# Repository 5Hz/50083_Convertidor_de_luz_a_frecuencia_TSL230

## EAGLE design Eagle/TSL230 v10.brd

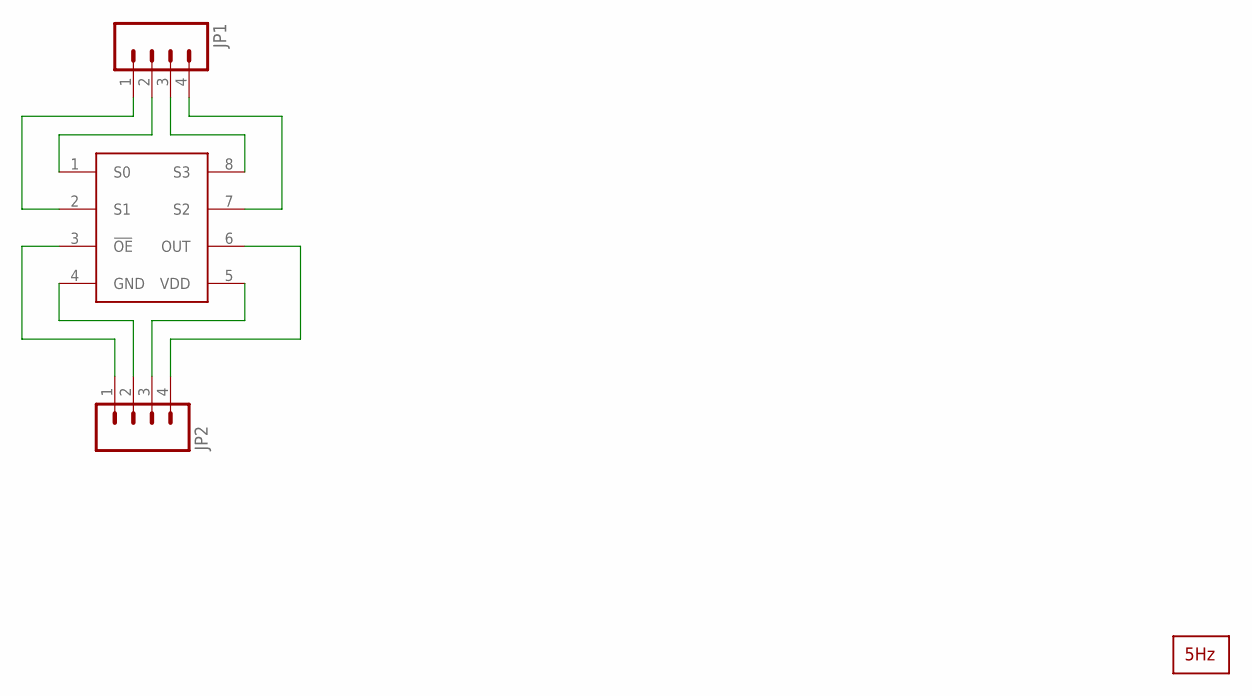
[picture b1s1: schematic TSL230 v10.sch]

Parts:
JP1, JP2: M04PTH; 1X04
U$1: TSL230RD; SOIC8
U$2: LOGO2_SILKL5MM; LARGO2_5MM

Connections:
unnamed: JP2.1, U$1.3 (!OE)
unnamed: JP2.2, U$1.4 (GND)
unnamed: JP2.4, U$1.6 (OUT)
unnamed: JP2.3, U$1.5 (VDD)
unnamed: JP1.1, U$1.2 (S1)
unnamed: JP1.2, U$1.1 (S0)
unnamed: JP1.3, U$1.8 (S3)
unnamed: JP1.4, U$1.7 (S2)

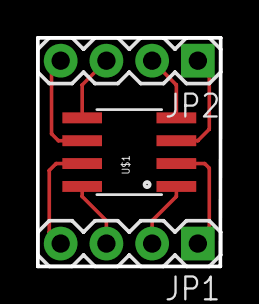
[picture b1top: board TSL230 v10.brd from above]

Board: 2 copper layers, 10.2 x 12.7 mm, 4 parts (1 on the bottom side), 8 nets.

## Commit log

2014-01-13 creación

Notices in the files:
parts and their libraries:
SparkFun: Licensing: CC v3.0 Share-Alike You are welcome to use this library for commercial purposes.
